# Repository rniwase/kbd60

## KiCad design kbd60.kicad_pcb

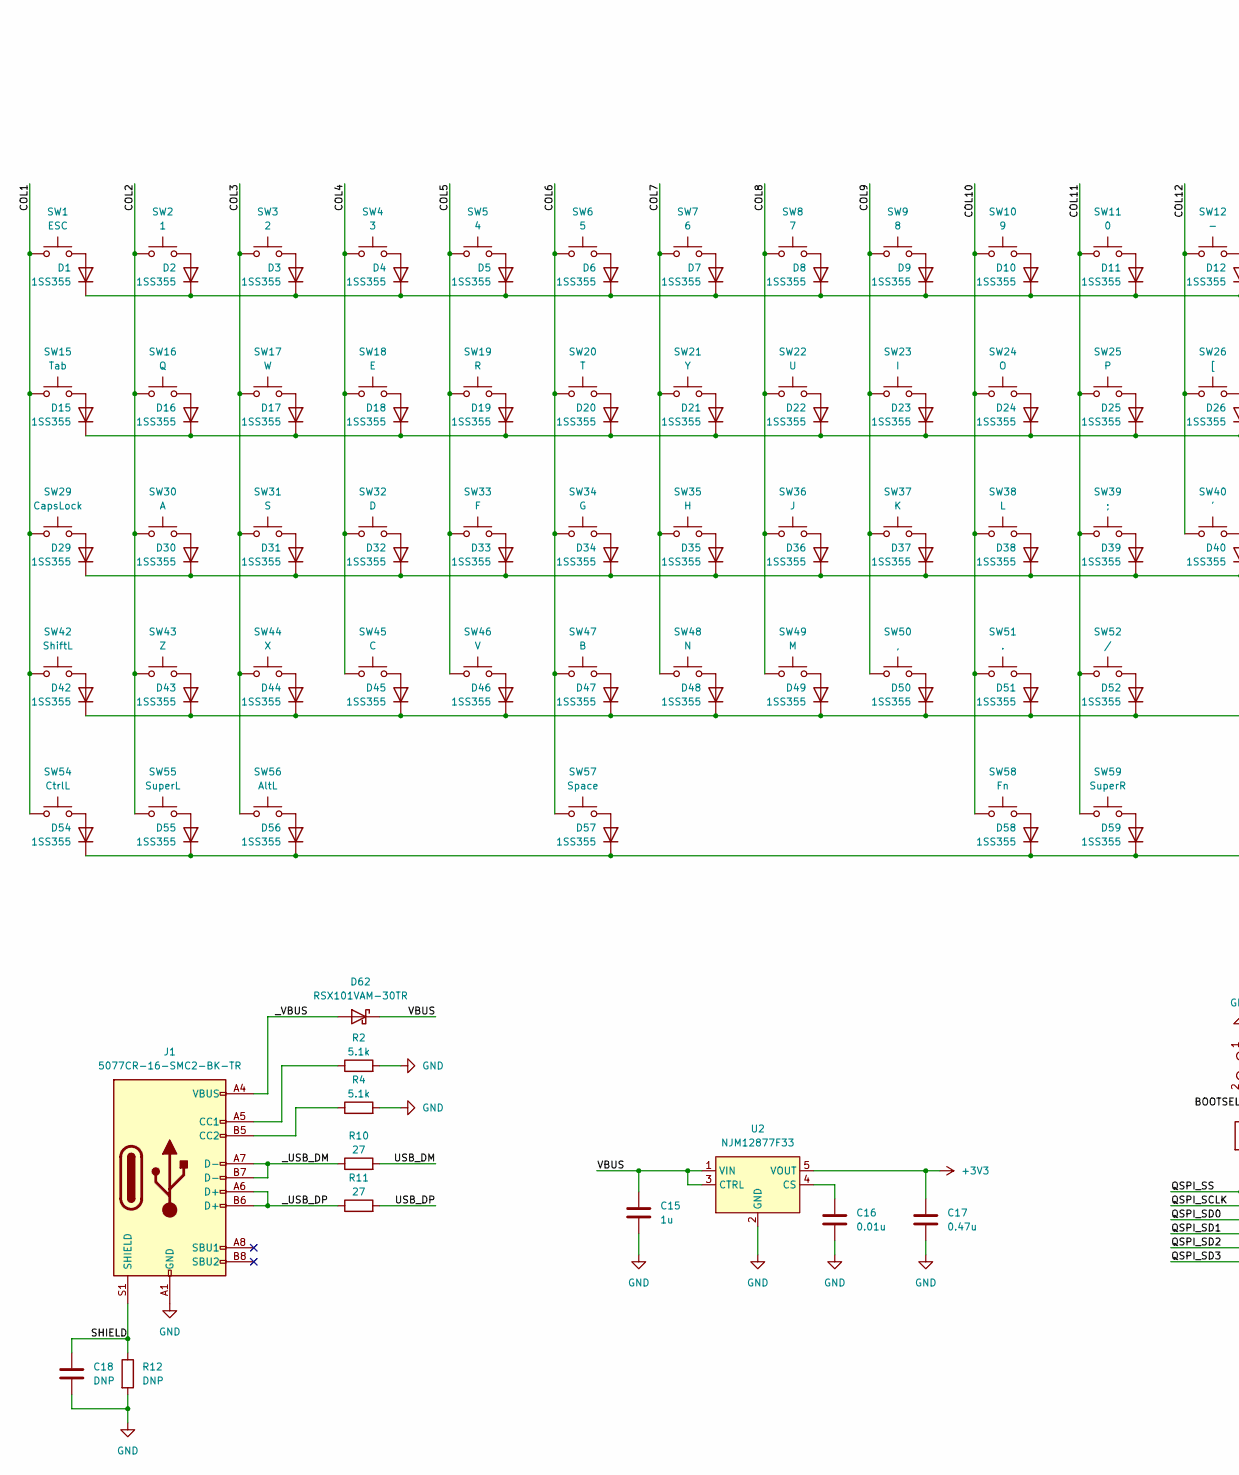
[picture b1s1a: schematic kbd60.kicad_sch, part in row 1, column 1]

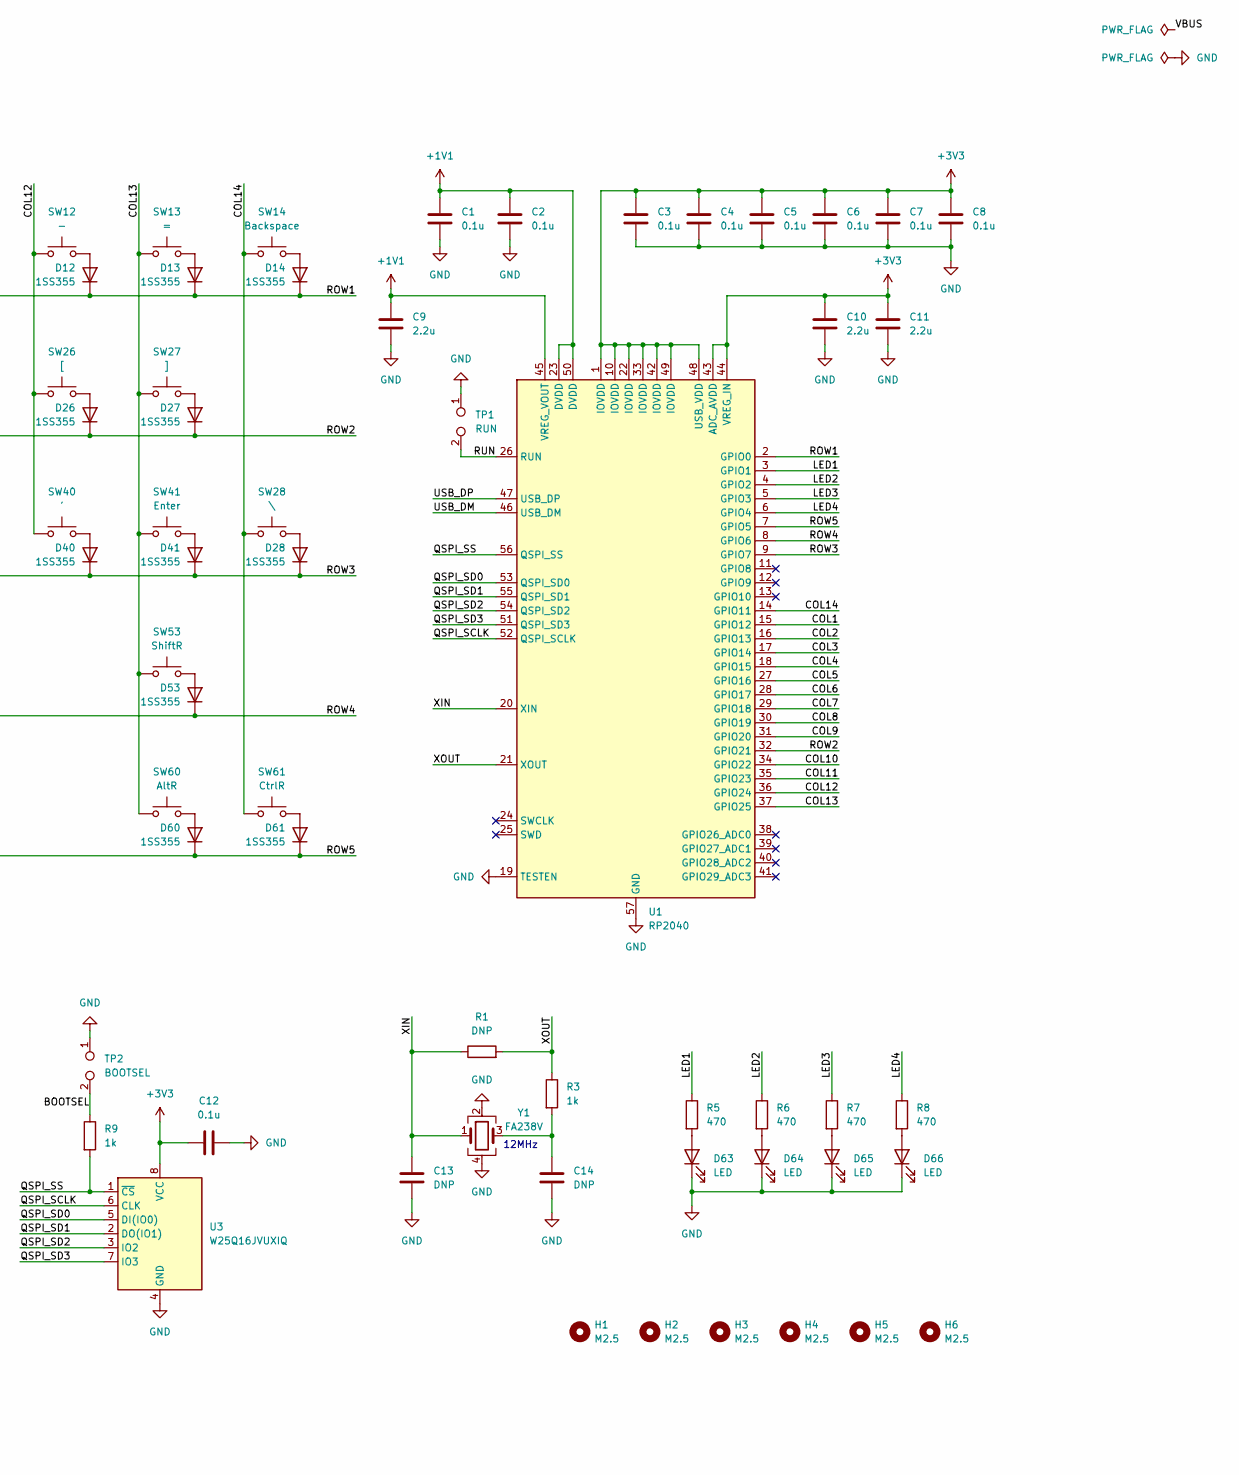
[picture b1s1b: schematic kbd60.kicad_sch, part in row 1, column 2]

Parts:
C1, C2, C3, C4, C5, C6, C7, C8, C12: 0.1u; C_0402_1005Metric
C9, C10, C11: 2.2u; C_0402_1005Metric
C13, C14, C18: DNP; C_0402_1005Metric
C15: 1u; C_0402_1005Metric
C16: 0.01u; C_0402_1005Metric
C17: 0.47u; C_0402_1005Metric
D1, D2, D3, D4, D5, D6, D7, D8, D9, D10, D11, D12, D13, D14, D15, D16, D17, D18, D19, D20, D21, D22, D23, D24, D25, D26, D27, D28, D29, D30, D31, D32, D33, D34, D35, D36, D37, D38, D39, D40, D41, D42, D43, D44, D45, D46, D47, D48, D49, D50, D51, D52, D53, D54, D55, D56, D57, D58, D59, D60, D61: 1SS355; D_SOD-323
D62: RSX101VAM-30TR; D_TUMD2
D63, D64, D65, D66: LED; LED_0603_1608Metric
H1, H2, H3, H4, H5, H6: M2.5; MountingHole_2.7mm_M2.5_ISO7380
J1: 5077CR-16-SMC2-BK-TR; USB_C_Receptacle_G-Switch_GT-USB-7010ASV
R1, R12: DNP; R_0402_1005Metric
R2, R4: 5.1k; R_0402_1005Metric
R3, R9: 1k; R_0402_1005Metric
R5, R6, R7, R8: 470; R_0402_1005Metric
R10, R11: 27; R_0402_1005Metric
SW1: ESC; SW_Cherry_MX_1.00u_PCB
SW2: 1; SW_Cherry_MX_1.00u_PCB
SW3: 2; SW_Cherry_MX_1.00u_PCB
SW4: 3; SW_Cherry_MX_1.00u_PCB
SW5: 4; SW_Cherry_MX_1.00u_PCB
SW6: 5; SW_Cherry_MX_1.00u_PCB
SW7: 6; SW_Cherry_MX_1.00u_PCB
SW8: 7; SW_Cherry_MX_1.00u_PCB
SW9: 8; SW_Cherry_MX_1.00u_PCB
SW10: 9; SW_Cherry_MX_1.00u_PCB
SW11: 0; SW_Cherry_MX_1.00u_PCB
SW12: -; SW_Cherry_MX_1.00u_PCB
SW13: =; SW_Cherry_MX_1.00u_PCB
SW14: Backspace; SW_Cherry_MX_2.00u_PCB
SW15: Tab; SW_Cherry_MX_1.50u_PCB
SW16: Q; SW_Cherry_MX_1.00u_PCB
SW17: W; SW_Cherry_MX_1.00u_PCB
SW18: E; SW_Cherry_MX_1.00u_PCB
SW19: R; SW_Cherry_MX_1.00u_PCB
SW20: T; SW_Cherry_MX_1.00u_PCB
SW21: Y; SW_Cherry_MX_1.00u_PCB
SW22: U; SW_Cherry_MX_1.00u_PCB
SW23: I; SW_Cherry_MX_1.00u_PCB
SW24: O; SW_Cherry_MX_1.00u_PCB
SW25: P; SW_Cherry_MX_1.00u_PCB
SW26: [; SW_Cherry_MX_1.00u_PCB
SW27: ]; SW_Cherry_MX_1.00u_PCB
SW28: \; SW_Cherry_MX_1.50u_PCB
SW29: CapsLock; SW_Cherry_MX_1.75u_PCB
SW30: A; SW_Cherry_MX_1.00u_PCB
SW31: S; SW_Cherry_MX_1.00u_PCB
SW32: D; SW_Cherry_MX_1.00u_PCB
SW33: F; SW_Cherry_MX_1.00u_PCB
SW34: G; SW_Cherry_MX_1.00u_PCB
SW35: H; SW_Cherry_MX_1.00u_PCB
SW36: J; SW_Cherry_MX_1.00u_PCB
SW37: K; SW_Cherry_MX_1.00u_PCB
SW38: L; SW_Cherry_MX_1.00u_PCB
SW39: ;; SW_Cherry_MX_1.00u_PCB
SW40: '; SW_Cherry_MX_1.00u_PCB
SW41: Enter; SW_Cherry_MX_2.25u_PCB
SW42: ShiftL; SW_Cherry_MX_2.25u_PCB
SW43: Z; SW_Cherry_MX_1.00u_PCB
SW44: X; SW_Cherry_MX_1.00u_PCB
SW45: C; SW_Cherry_MX_1.00u_PCB
SW46: V; SW_Cherry_MX_1.00u_PCB
SW47: B; SW_Cherry_MX_1.00u_PCB
SW48: N; SW_Cherry_MX_1.00u_PCB
SW49: M; SW_Cherry_MX_1.00u_PCB
SW50: ,; SW_Cherry_MX_1.00u_PCB
SW51: .; SW_Cherry_MX_1.00u_PCB
SW52: /; SW_Cherry_MX_1.00u_PCB
SW53: ShiftR; SW_Cherry_MX_2.75u_PCB
SW54: CtrlL; SW_Cherry_MX_1.25u_PCB
SW55: SuperL; SW_Cherry_MX_1.25u_PCB
SW56: AltL; SW_Cherry_MX_1.25u_PCB
SW57: Space; SW_Cherry_MX_6.25u_PCB
SW58: Fn; SW_Cherry_MX_1.25u_PCB
SW59: SuperR; SW_Cherry_MX_1.25u_PCB
SW60: AltR; SW_Cherry_MX_1.25u_PCB
SW61: CtrlR; SW_Cherry_MX_1.25u_PCB
TP1: RUN; TestPoint_2Pads_Pitch2.54mm_Drill0.8mm
TP2: BOOTSEL; TestPoint_2Pads_Pitch2.54mm_Drill0.8mm
U1: RP2040; QFN-56-1EP_7x7mm_P0.4mm_EP3.2x3.2mm
U2: NJM12877F33; SOT-23-5
U3: W25Q16JVUXIQ; USON-8_2x3mm_P0.5mm
Y1: FA238V; Crystal_SMD_SeikoEpson_FA238V-4Pin_3.2x2.5mm

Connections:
+1V1: C1.2, C2.2, C9.2, U1.23 (DVDD), U1.45 (VREG_VOUT), U1.50 (DVDD)
+3V3: C3.2, C4.2, C5.2, C6.2, C7.2, C8.2, C10.2, C11.2, C12.1, C17.1, U1.1 (IOVDD), U1.10 (IOVDD), U1.22 (IOVDD), U1.33 (IOVDD), U1.42 (IOVDD), U1.43 (ADC_AVDD), U1.44 (VREG_IN), U1.48 (USB_VDD), U1.49 (IOVDD), U2.5 (VOUT), U3.8 (VCC)
/BOOTSEL: R9.1, TP2.2
/COL1: SW1.2, SW15.2, SW29.2, SW42.2, SW54.2, U1.15 (GPIO12)
/COL2: SW2.2, SW16.2, SW30.2, SW43.2, SW55.2, U1.16 (GPIO13)
/COL3: SW3.2, SW17.2, SW31.2, SW44.2, SW56.2, U1.17 (GPIO14)
/COL4: SW4.2, SW18.2, SW32.2, SW45.2, U1.18 (GPIO15)
/COL5: SW5.2, SW19.2, SW33.2, SW46.2, U1.27 (GPIO16)
/COL6: SW6.2, SW20.2, SW34.2, SW47.2, SW57.2, U1.28 (GPIO17)
/COL7: SW7.2, SW21.2, SW35.2, SW48.2, U1.29 (GPIO18)
/COL8: SW8.2, SW22.2, SW36.2, SW49.2, U1.30 (GPIO19)
/COL9: SW9.2, SW23.2, SW37.2, SW50.2, U1.31 (GPIO20)
/COL10: SW10.2, SW24.2, SW38.2, SW51.2, SW58.2, U1.34 (GPIO22)
/COL11: SW11.2, SW25.2, SW39.2, SW52.2, SW59.2, U1.35 (GPIO23)
/COL12: SW12.2, SW26.2, SW40.2, U1.36 (GPIO24)
/COL13: SW13.2, SW27.2, SW41.2, SW53.2, SW60.2, U1.37 (GPIO25)
/COL14: SW14.2, SW28.2, SW61.2, U1.14 (GPIO11)
/LED1: R5.1, U1.3 (GPIO1)
/LED2: R6.1, U1.4 (GPIO2)
/LED3: R7.1, U1.5 (GPIO3)
/LED4: R8.1, U1.6 (GPIO4)
/QSPI_SCLK: U1.52 (QSPI_SCLK), U3.6 (CLK)
/QSPI_SD0: U1.53 (QSPI_SD0), U3.5 (DI(IO0))
/QSPI_SD1: U1.55 (QSPI_SD1), U3.2 (DO(IO1))
/QSPI_SD2: U1.54 (QSPI_SD2), U3.3 (IO2)
/QSPI_SD3: U1.51 (QSPI_SD3), U3.7 (IO3)
/QSPI_SS: R9.2, U1.56 (QSPI_SS), U3.1 (~CS)
/ROW1: D1.1 (K), D2.1 (K), D3.1 (K), D4.1 (K), D5.1 (K), D6.1 (K), D7.1 (K), D8.1 (K), D9.1 (K), D10.1 (K), D11.1 (K), D12.1 (K), D13.1 (K), D14.1 (K), U1.2 (GPIO0)
/ROW2: D15.1 (K), D16.1 (K), D17.1 (K), D18.1 (K), D19.1 (K), D20.1 (K), D21.1 (K), D22.1 (K), D23.1 (K), D24.1 (K), D25.1 (K), D26.1 (K), D27.1 (K), U1.32 (GPIO21)
/ROW3: D28.1 (K), D29.1 (K), D30.1 (K), D31.1 (K), D32.1 (K), D33.1 (K), D34.1 (K), D35.1 (K), D36.1 (K), D37.1 (K), D38.1 (K), D39.1 (K), D40.1 (K), D41.1 (K), U1.9 (GPIO7)
/ROW4: D42.1 (K), D43.1 (K), D44.1 (K), D45.1 (K), D46.1 (K), D47.1 (K), D48.1 (K), D49.1 (K), D50.1 (K), D51.1 (K), D52.1 (K), D53.1 (K), U1.8 (GPIO6)
/ROW5: D54.1 (K), D55.1 (K), D56.1 (K), D57.1 (K), D58.1 (K), D59.1 (K), D60.1 (K), D61.1 (K), U1.7 (GPIO5)
/RUN: TP1.2, U1.26 (RUN)
/SHIELD: C18.1, J1.S1 (SHIELD), R12.1
/USB_DM: R10.2, U1.46 (USB_DM)
/USB_DP: R11.2, U1.47 (USB_DP)
/VBUS: C15.1, D62.1 (K), U2.1 (VIN), U2.3 (CTRL)
/XIN: C13.1, R1.1, U1.20 (XIN), Y1.1
/XOUT: R1.2, R3.1, U1.21 (XOUT)
/_USB_DM: J1.A7 (D-), J1.B7 (D-), R10.1
/_USB_DP: J1.A6 (D+), J1.B6 (D+), R11.1
/_VBUS: D62.2 (A), J1.A4 (VBUS), J1.A9 (VBUS), J1.B4 (VBUS), J1.B9 (VBUS)
GND: C1.1, C2.1, C3.1, C4.1, C5.1, C6.1, C7.1, C8.1, C9.1, C10.1, C11.1, C12.2, C13.2, C14.2, C15.2, C16.2, C17.2, C18.2, D63.1 (K), D64.1 (K), D65.1 (K), D66.1 (K), J1.A1 (GND), J1.A12 (GND), J1.B1 (GND), J1.B12 (GND), R2.2, R4.2, R12.2, TP1.1, TP2.1, U1.19 (TESTEN), U1.57 (GND), U2.2 (GND), U3.4 (GND), Y1.2, Y1.4
unnamed: C14.1, R3.2, Y1.3
unnamed: D1.2 (A), SW1.1
unnamed: D2.2 (A), SW2.1
unnamed: D3.2 (A), SW3.1
unnamed: D4.2 (A), SW4.1
unnamed: D5.2 (A), SW5.1
unnamed: D6.2 (A), SW6.1
unnamed: D7.2 (A), SW7.1
unnamed: D8.2 (A), SW8.1
unnamed: D9.2 (A), SW9.1
unnamed: D10.2 (A), SW10.1
unnamed: D11.2 (A), SW11.1
unnamed: D12.2 (A), SW12.1
unnamed: D13.2 (A), SW13.1
unnamed: D14.2 (A), SW14.1
unnamed: D15.2 (A), SW15.1
unnamed: D16.2 (A), SW16.1
unnamed: D17.2 (A), SW17.1
unnamed: D18.2 (A), SW18.1
unnamed: D19.2 (A), SW19.1
unnamed: D20.2 (A), SW20.1
unnamed: D21.2 (A), SW21.1
unnamed: D22.2 (A), SW22.1
unnamed: D23.2 (A), SW23.1
unnamed: D24.2 (A), SW24.1
unnamed: D25.2 (A), SW25.1
unnamed: D26.2 (A), SW26.1
unnamed: D27.2 (A), SW27.1
unnamed: D28.2 (A), SW28.1
unnamed: D29.2 (A), SW29.1
unnamed: D30.2 (A), SW30.1
unnamed: D31.2 (A), SW31.1
unnamed: D32.2 (A), SW32.1
unnamed: D33.2 (A), SW33.1
unnamed: D34.2 (A), SW34.1
unnamed: D35.2 (A), SW35.1
unnamed: D36.2 (A), SW36.1
unnamed: D37.2 (A), SW37.1
unnamed: D38.2 (A), SW38.1
unnamed: D39.2 (A), SW39.1
unnamed: D40.2 (A), SW40.1
unnamed: D41.2 (A), SW41.1
unnamed: D42.2 (A), SW42.1
unnamed: D43.2 (A), SW43.1
unnamed: D44.2 (A), SW44.1
unnamed: D45.2 (A), SW45.1
unnamed: D46.2 (A), SW46.1
unnamed: D47.2 (A), SW47.1
unnamed: D48.2 (A), SW48.1
unnamed: D49.2 (A), SW49.1
unnamed: D50.2 (A), SW50.1
unnamed: D51.2 (A), SW51.1
unnamed: D52.2 (A), SW52.1
unnamed: D53.2 (A), SW53.1
unnamed: D54.2 (A), SW54.1
unnamed: D55.2 (A), SW55.1
unnamed: D56.2 (A), SW56.1
unnamed: D57.2 (A), SW57.1
unnamed: D58.2 (A), SW58.1
unnamed: D59.2 (A), SW59.1
unnamed: D60.2 (A), SW60.1
unnamed: D61.2 (A), SW61.1
unnamed: D63.2 (A), R5.2
unnamed: D64.2 (A), R6.2
unnamed: D65.2 (A), R7.2
unnamed: D66.2 (A), R8.2
unnamed: J1.A5 (CC1), R2.1
unnamed: J1.B5 (CC2), R4.1
unnamed: C16.1, U2.4 (CS)

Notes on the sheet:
12MHz

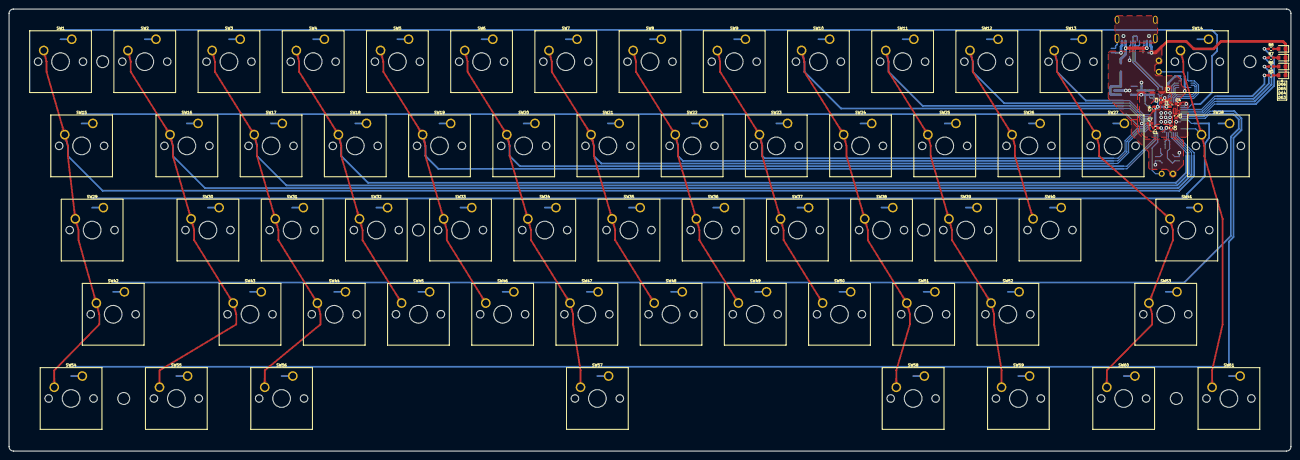
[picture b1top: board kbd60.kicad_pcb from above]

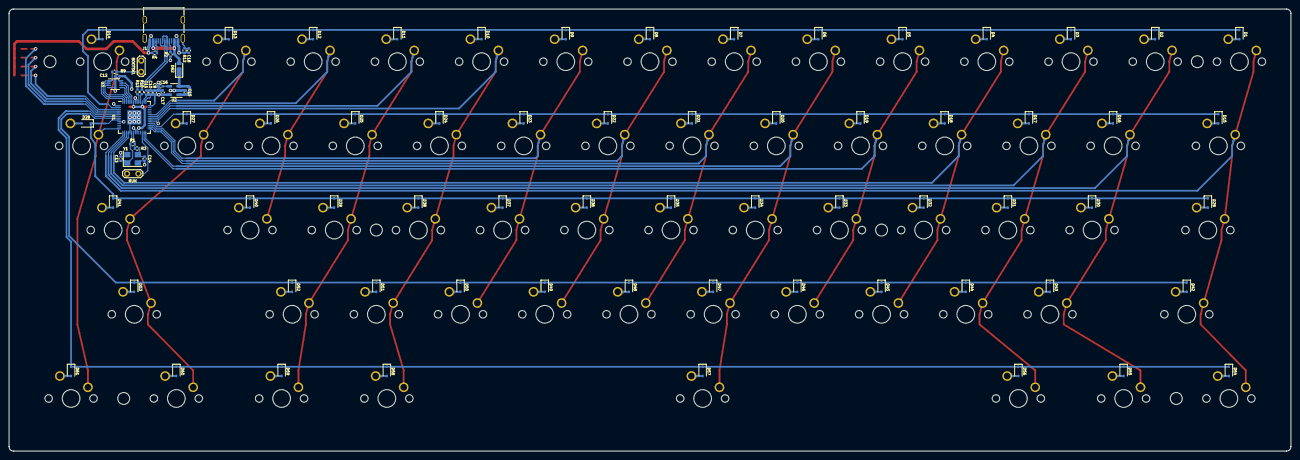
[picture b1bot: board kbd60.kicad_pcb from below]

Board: 2 copper layers, 290.0 x 100.0 mm, 170 parts (87 on the bottom side), 112 nets.

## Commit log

2024-02-12 wip: pcb routed
2024-02-12 wip: re-route columns
2024-02-12 wip: update F.Cu
2024-02-12 wip: update footprint libs
2024-02-12 DRC ok
2024-02-12 add teardrops
2024-02-13 add mount holes
2024-02-23 update route and edge cut
